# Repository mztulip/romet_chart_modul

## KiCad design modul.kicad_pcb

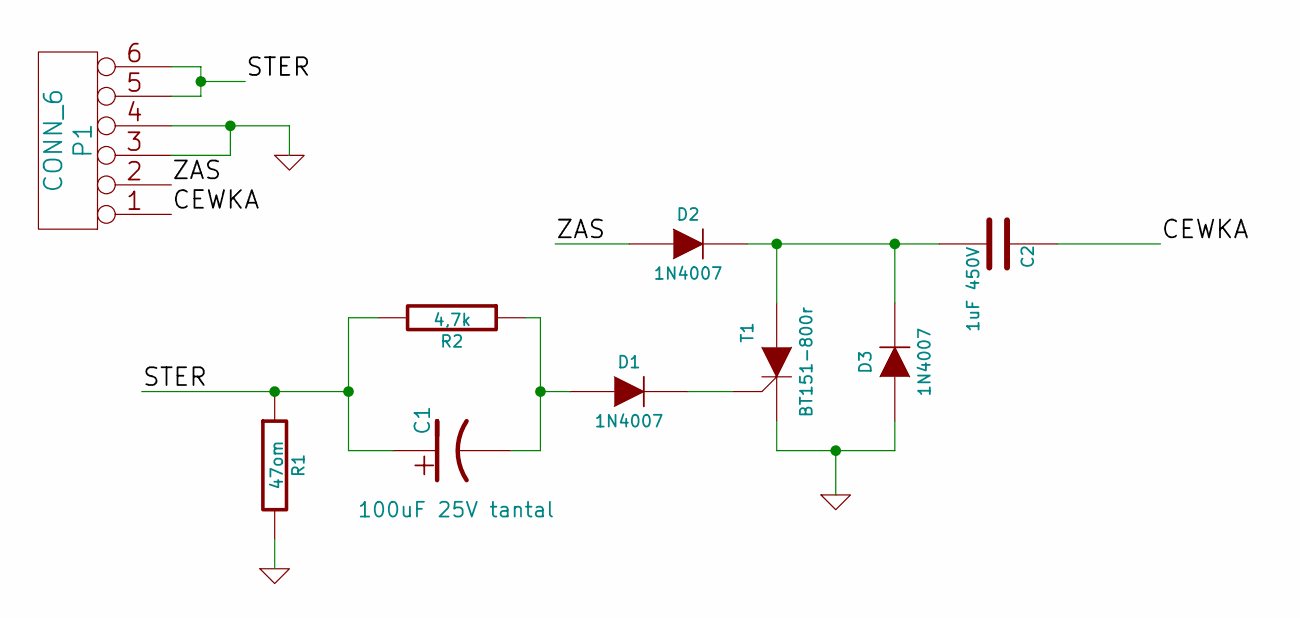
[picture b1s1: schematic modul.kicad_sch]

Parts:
C1: 100uF 25V tantal
C2: 1uF 450V
D1, D2, D3: 1N4007
P1: CONN_6
R1: 47om
R2: 4,7k
T1: BT151-800r

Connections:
/CEWKA: C2.1, P1.1
/STER: C1.1, P1.5, P1.6, R1.1, R2.2
/ZAS: D2.1 (A), P1.2
GND: D3.1 (A), P1.3, P1.4, R1.2, T1.K
unnamed: C1.2, D1.1 (A), R2.1
unnamed: C2.2, D2.2 (K), D3.2 (K), T1.A
unnamed: D1.2 (K), T1.G

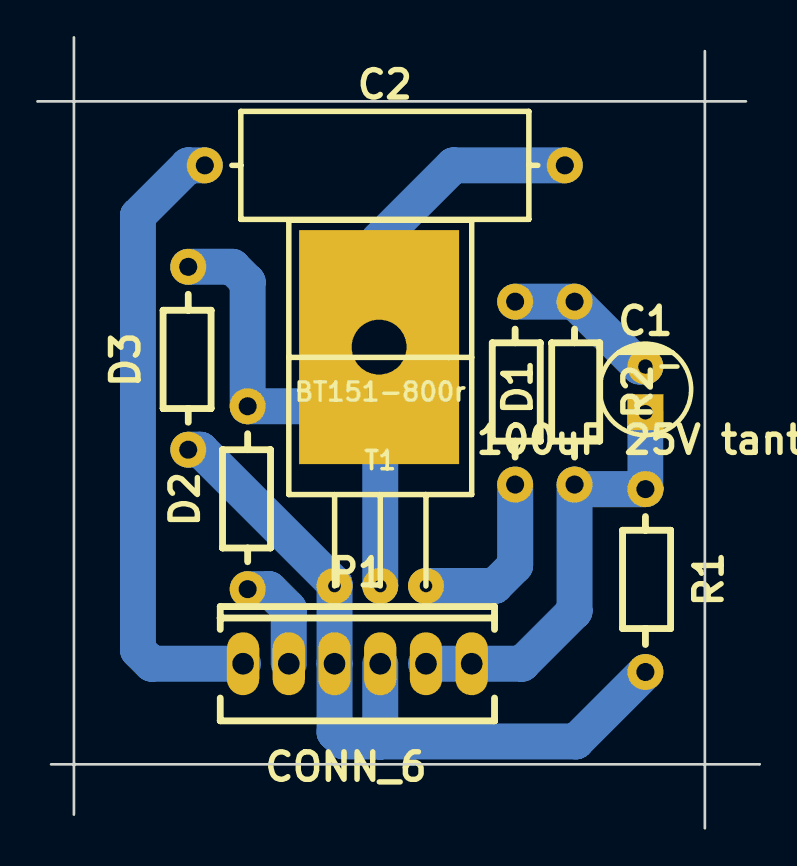
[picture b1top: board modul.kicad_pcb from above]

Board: 2 copper layers, 40.1 x 43.9 mm, 9 parts (0 on the bottom side), 7 nets.

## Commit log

2020-05-13 Project files
2024-06-10 project updated with photos, converted to kicad 7, cleaned form backups
2024-06-10 schematics added
